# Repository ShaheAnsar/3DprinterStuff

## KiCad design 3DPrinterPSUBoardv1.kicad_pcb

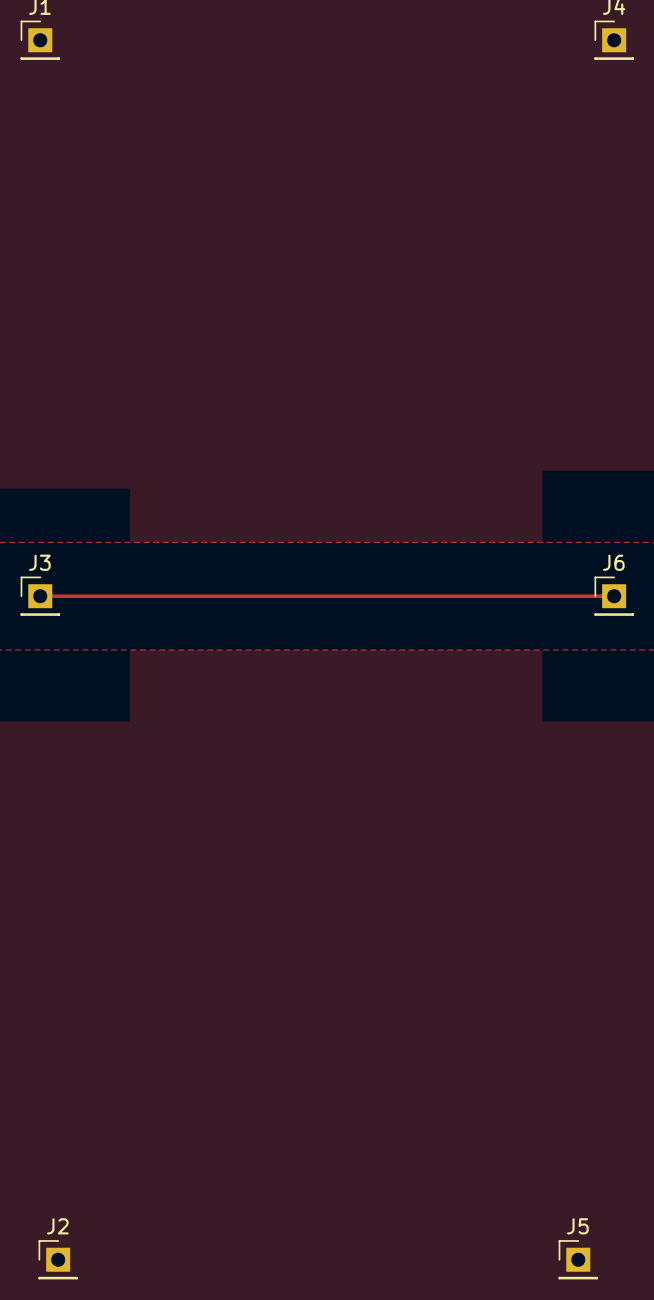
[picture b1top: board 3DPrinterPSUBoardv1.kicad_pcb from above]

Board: 2 copper layers, 6 parts (0 on the bottom side), 3 nets.

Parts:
J1: 12VIn; PinHeader_1x01_P2.54mm_Vertical
J2: GNDIn; PinHeader_1x01_P2.54mm_Vertical
J3, J6: PS_ON; PinHeader_1x01_P2.54mm_Vertical
J4: 12VOut; PinHeader_1x01_P2.54mm_Vertical
J5: GNDOut; PinHeader_1x01_P2.54mm_Vertical

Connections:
unnamed: J1.1, J4.1
unnamed: J2.1, J5.1
unnamed: J3.1, J6.1

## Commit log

2021-07-20 Create LICENSE
